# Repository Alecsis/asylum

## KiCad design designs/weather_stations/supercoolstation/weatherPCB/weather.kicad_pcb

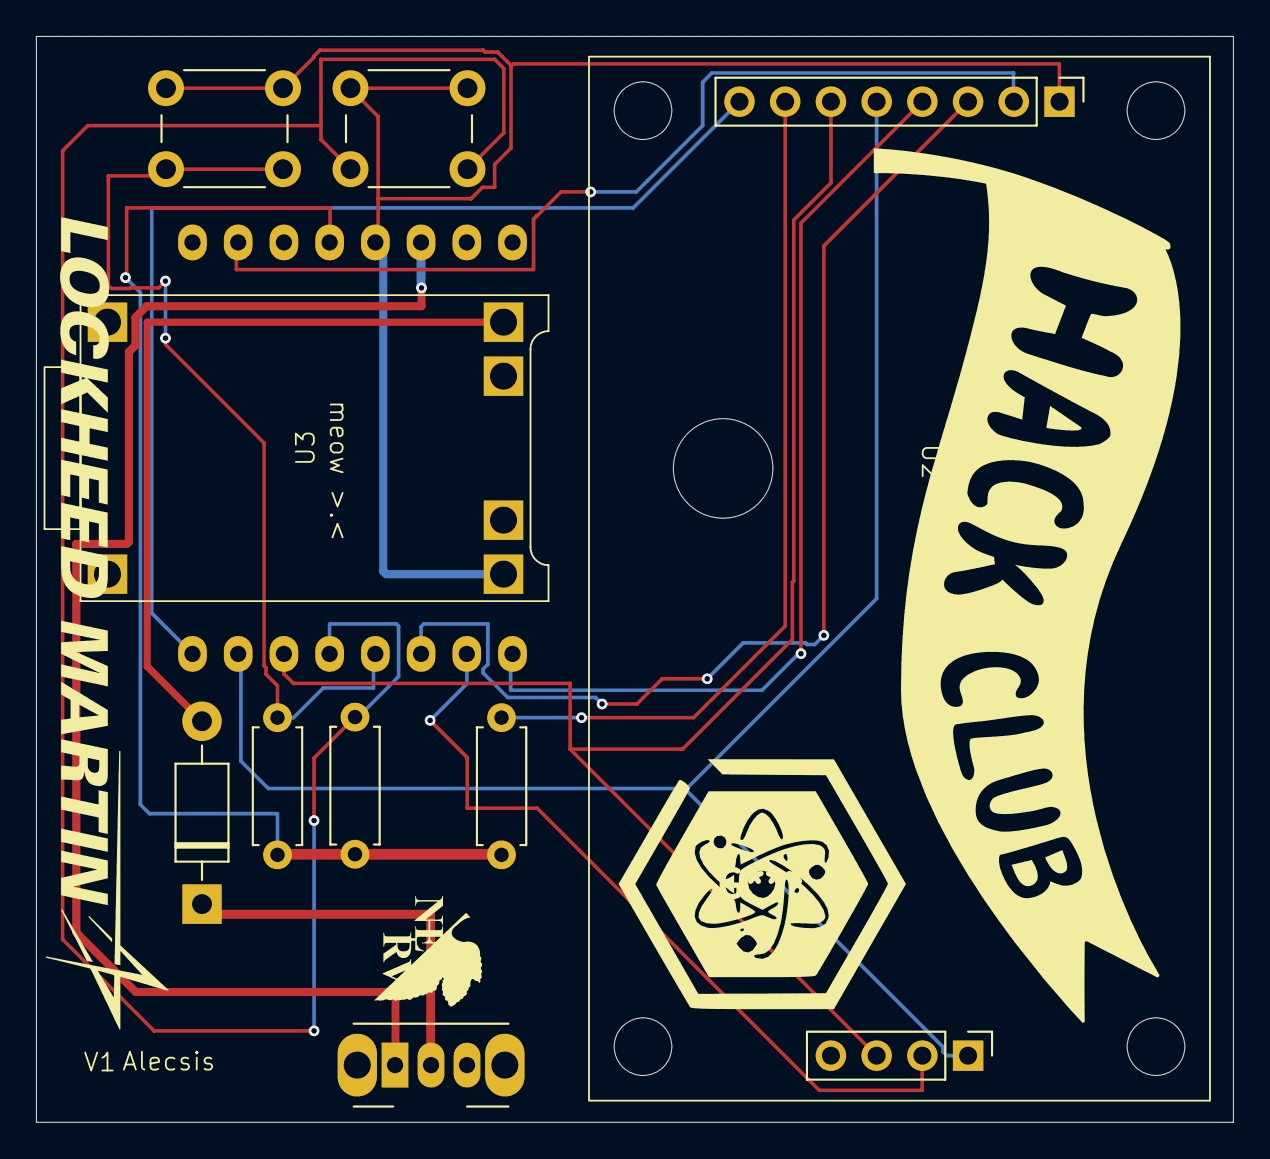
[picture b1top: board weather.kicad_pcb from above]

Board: 2 copper layers, 66.5 x 60.3 mm, 10 parts (1 on the bottom side), 15 nets.

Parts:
D1: 1N5817; D_DO-41_SOD81_P10.16mm_Horizontal
R2: 10; R_Axial_DIN0207_L6.3mm_D2.5mm_P7.62mm_Horizontal
R5, R6: 10K; R_Axial_DIN0207_L6.3mm_D2.5mm_P7.62mm_Horizontal
SW1, SW2: SW_Push; SW_PUSH_6mm_H9.5mm
SW3: SW_SPDT; SW_Slide_SPDT_Angled_CK_OS102011MA1Q
U1: WEMOS_C3_mini
U2: TFT_ST7735_SD
U3: TP4056

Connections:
+3.3V: R2.2, R5.1, R6.1, U1.12 (3.3V)
AO: U1.1 (A1), U2.4 (AO)
B1: R5.2, SW1.1, U1.4 (A4)
B2: R6.2, SW2.1, U1.5 (A5)
Batt_Out: D1.2 (A), U3.2 (OUT+)
CS: U1.10, U2.2 (~CS)
GND: SW1.2, SW2.2, U1.13 (GND), U2.1 (GND), U3.3 (OUT-)
MISO: U1.2 (A2), U2.10 (SD_MISO)
MOSI: U1.7 (7/RGB_LED), U2.5 (SDA), U2.9 (SD_MOSI)
unnamed: D1.1 (K), SW3.2 (B)
unnamed: R2.1, U2.7 (LED)
RESET: U1.3 (A3), U2.3 (RESET)
SCK: U1.6, U2.6 (SCK), U2.11 (SD_SCK)
SD_CS: U1.8, U2.8 (SD_CS)
VCC: SW3.1 (A), U1.14 (VBUS)
